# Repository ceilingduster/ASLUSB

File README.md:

# ASLUSB
Very rough schematic for a Allstar USB FOB board by VA3IAN

# Schematic
[Schematic](asl-allstar.pdf)

# Credits
[SHARI-Schematic](https://hamprojects.info/shari/shari-schematic/)

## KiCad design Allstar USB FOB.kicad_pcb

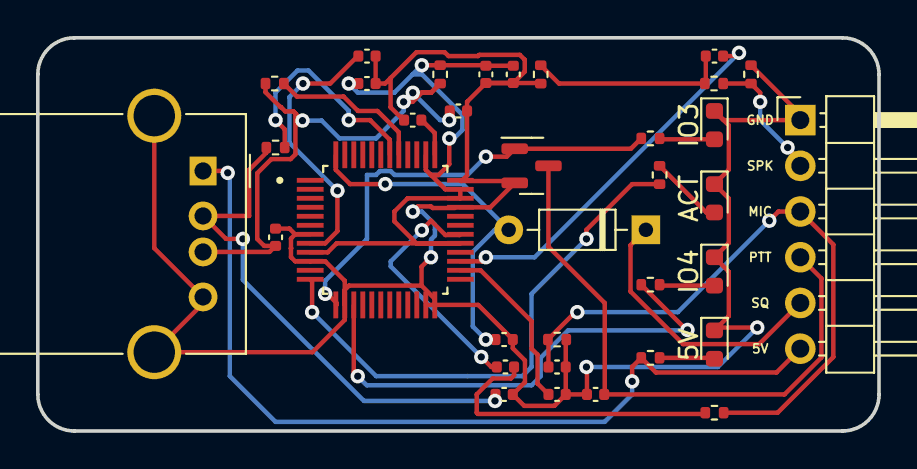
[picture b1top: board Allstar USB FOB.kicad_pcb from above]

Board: 2 copper layers, 46.7 x 21.8 mm, 35 parts (0 on the bottom side), 26 nets.

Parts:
C1, C2: 100pF; C_0402_1005Metric
C1#2, C7, C11, C12, C13: 4.7uF; C_0402_1005Metric
C3: 0.1uF; C_0402_1005Metric
C4: 4.78uF; C_0402_1005Metric
C5: 100nF; C_0402_1005Metric
C6, C9: 10uF; C_0402_1005Metric
C8, C10: 1000pF; C_0402_1005Metric
D1: 1N4148; D_DO-35_SOD27_P7.62mm_Horizontal
D2: ACT; LED_0603_1608Metric
D3: IO3; LED_0603_1608Metric
D4: IO4; LED_0603_1608Metric
D5: 5V; LED_0603_1608Metric
J1: USB_A; USB_A_Molex_67643_Horizontal
J2: Conn_01x06_Male; PinHeader_1x06_P2.54mm_Horizontal
Q1: 2N7002; SOT-23
R1, R6: 1.5k; R_0402_1005Metric
R2, R3: 22; R_0402_1005Metric
R4, R7, R8, R9: 390; R_0402_1005Metric
R5, R11: 10k; R_0402_1005Metric
R10: OPEN; R_0402_1005Metric
R12: 1000pF; R_0402_1005Metric
U1: CM119B; QFP50P900X900X160-48N

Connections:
DREG18: C11.1, U1.8 (DREG18)
DREG33: C3.2, C4.2, C12.1, R1.2, U1.9 (DREG33), U1.29 (AVDD), U1.34 (AVDD), U1.35 (DVDD), U1.38 (MSEL)
DREG36: C13.1, U1.37 (AREG36)
GND: C1.2, C1#2.2, C2.2, C3.1, C4.1, C5.2, C7.2, C8.2, C10.2, C11.2, C12.2, C13.2, D2.1 (K), D3.1 (K), D4.1 (K), D5.1 (K), J1.4 (GND), J1.5 (Shield), J2.1, Q1.2 (S), R6.2, R10.2, R12.2, U1.7 (PWRSEL), U1.10 (MODE), U1.14 (DVSS), U1.23 (TEST), U1.24 (AVSS), U1.33 (AVSS), U1.36 (DVSS)
MICIN: C8.1, J2.3, R5.2, R6.1
MIC_PTT: C10.1, J2.4, Q1.3 (D)
unnamed: C1.1, C1#2.1, J1.3 (D+), R1.1, R2.1
unnamed: C2.1, J1.2 (D-), R3.1
unnamed: C6.1, U1.30 (LOL)
unnamed: C6.2, R5.1
unnamed: C7.1, U1.26 (VREF)
unnamed: C9.1, R10.1, R11.1
unnamed: C9.2, U1.27 (MICIN)
unnamed: D2.2 (A), R4.2
unnamed: D3.2 (A), R7.2
unnamed: D4.2 (A), R8.2
unnamed: D5.2 (A), R9.2
unnamed: Q1.1 (G), R7.1, U1.13 (GPIO3)
unnamed: R2.2, U1.41 (USBDP)
unnamed: R3.2, U1.42 (USBDM)
unnamed: R4.1, U1.12 (LEDO)
unnamed: R8.1, U1.15 (GPIO4)
SPEAKER: J2.2, R11.2, R12.1
SQUELCH: D1.1 (K), J2.5
USB_5V: J1.1 (VBUS), J2.6, R9.1
VOLDN: C5.1, D1.2 (A), U1.48 (VOLDN)
